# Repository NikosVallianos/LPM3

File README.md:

# LPM3 front-end #

The LPM3 is a device to measure light pollution on sea turtle nesting beaches. This repository focuses on the development of the front-end of the device, which can be used separately by any programmable device with an I²C and a SPI interface, such as an arduino, raspberry pi, or a suitable USB adapter.

The LPM3 front-end consists of a high sensitivity photometer and a regular sensitivity single-chip lux meter, an accelerometer, and a magnetometer all laid out on a single printed circuit board.

## Ultra-low dark current photodiode

The core of the LPM3 front-end is Hamamatsu's S1133, an ultra-low dark current visible light photodiode. A transimpedance amplifier with a 1GOhm feedback resistor gives a theoretical output of 1V per 0.164 lux. With a 12-bit ADC and a 2.5V reference, we can get a sensitivity of 0.0001 lux. The LPM3 is equipped with a 16-bit ADC, giving an absurd theoretical sensitivity of 0.00000625lux. Imperfections in the circuits and component manufacturing are expected to 

## Generic lux meter

The high sensitivity photodiode circuit is unable to measure any illuminance higher than 0.41lux. For this reason, and to serve as a crude source of self-calubration reference, the OPT3001 single-chip lux meter by Texas Instruments was incorporated in the LPM3 font-end. This lux meter is capable of measurements from 0.01 lux all the way up to daylight. This should cover all foreseeable light pollution conditions from pitch black all the way to in front of spotlights that are sometimes used to safeguard beach equipment.

## Accelerometer

All light pollution measurements should be taken at a horizontal plane, which is where hatchlings and sea turtles scan to perceive ambient light. An embedded accelerometer can either ensure this condition or be used to include device orientation in the dataset.

## Magnetometer

A magnetometer is the only way to know what direction a specific light pollution measurement was taken from.

## License
The LPM3 depository integrates hardware design, firmware source code, desktop software, and supporting documentation. These are licensed as follows:
- Hardware design files are licensed under the CERN Open Hardware License,
- Software source code files are licensed under the GNU GPL v3 license,
- Documentation files are licensed under the GNU Free Documentation License,
- Videos are licensed under Creative Commons Attribution-ShareAlike 4.0 International.

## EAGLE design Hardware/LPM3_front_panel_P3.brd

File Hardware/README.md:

This folder contains the hardware PCB design files, bill of materials, notes, data sheet links, and other details to help you manufacture a LPM3.
The hardware elements of the LPM3 project are licensed under the CERN Open Source Hardware license found here (link missing).

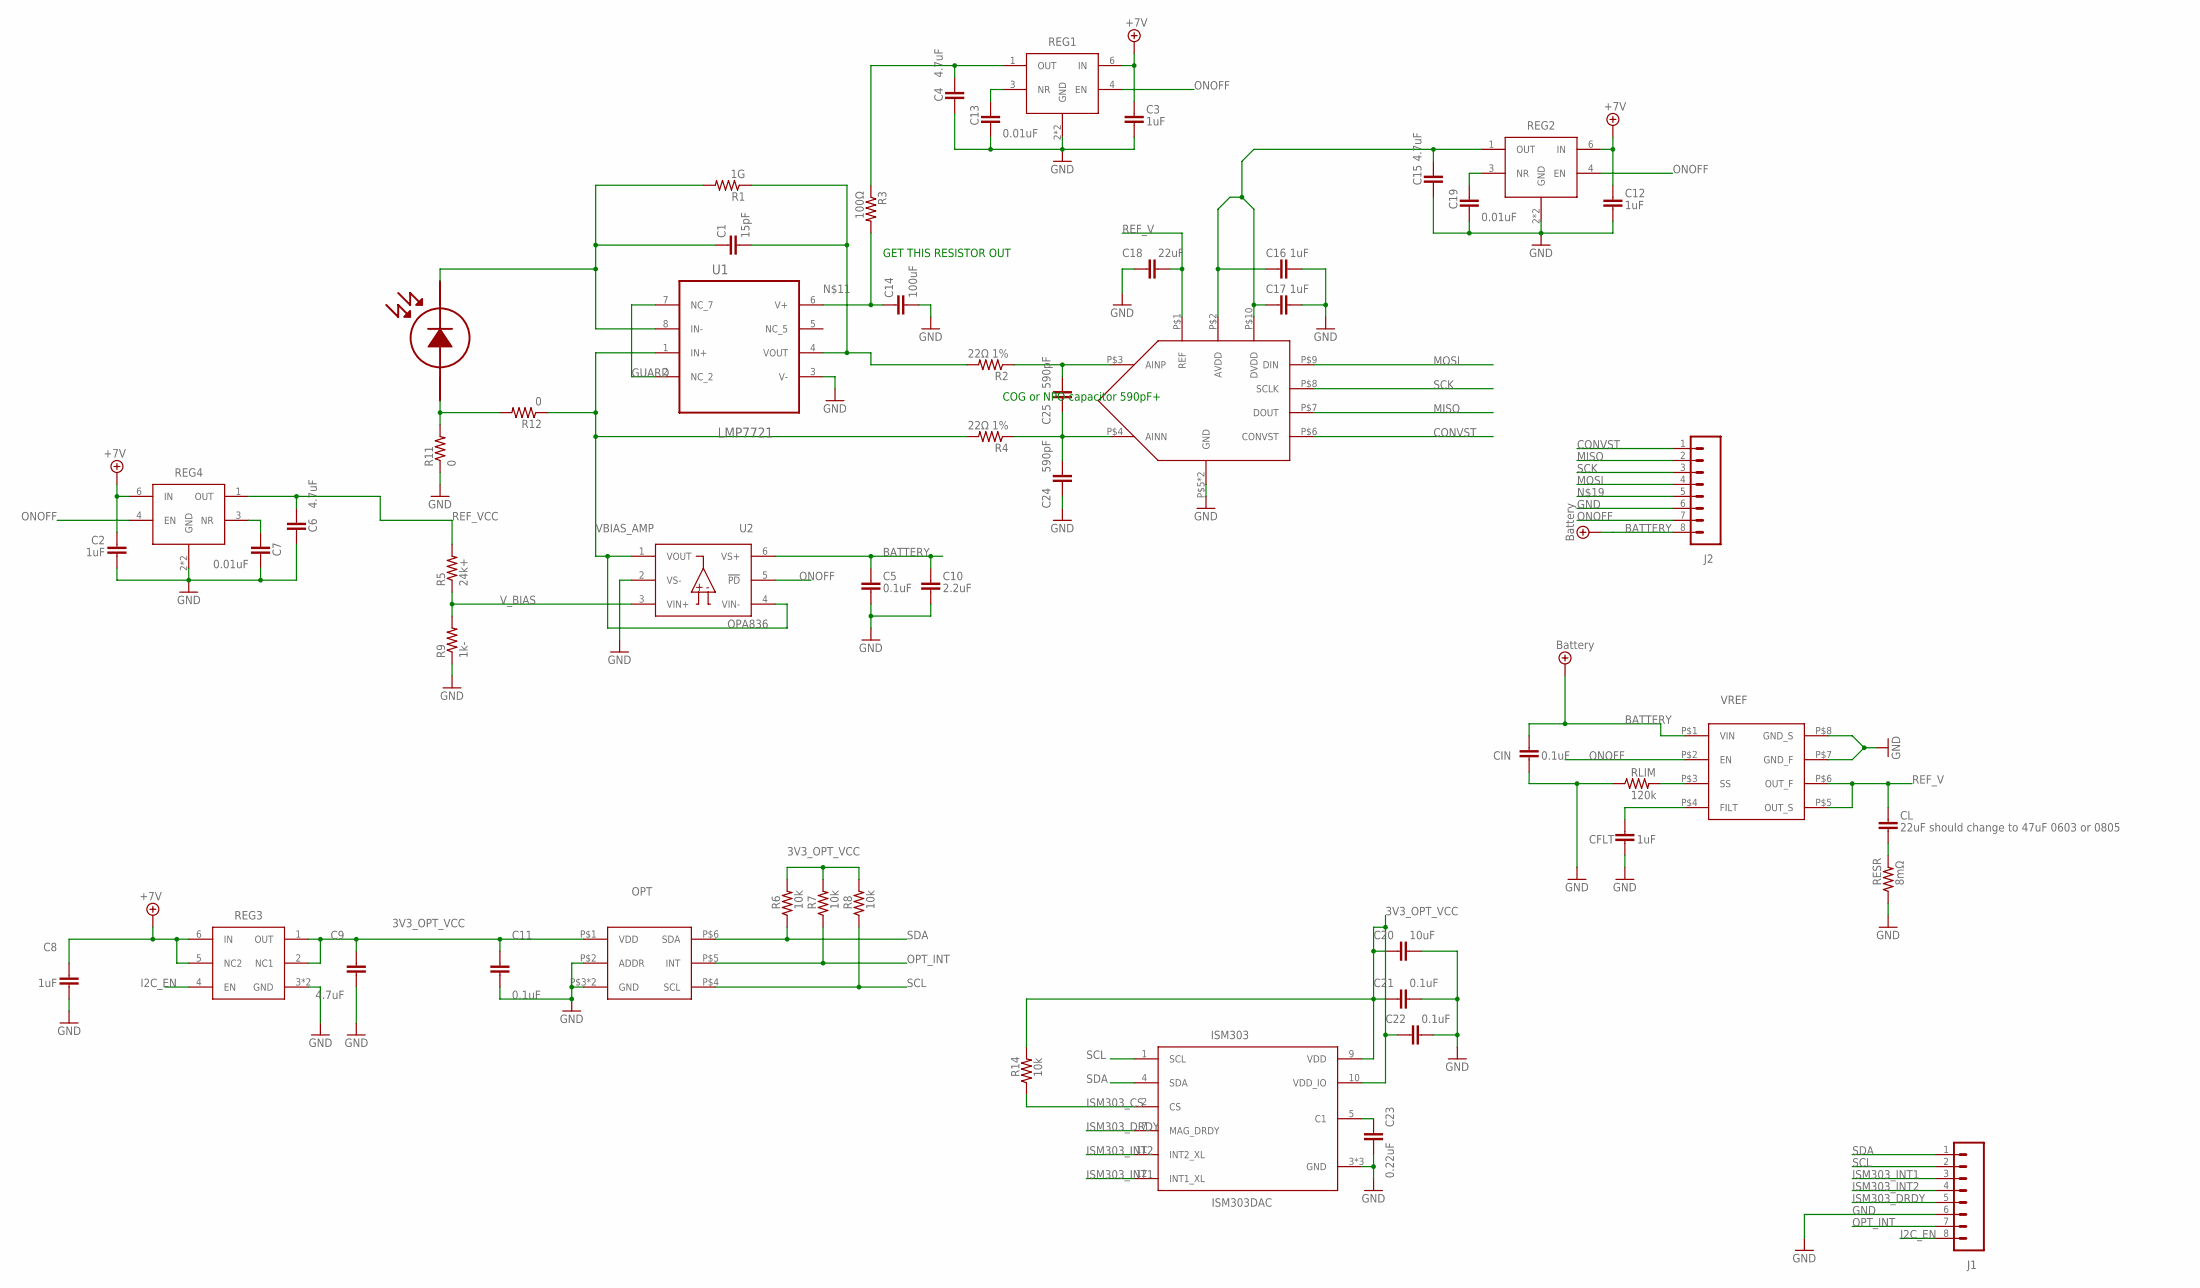
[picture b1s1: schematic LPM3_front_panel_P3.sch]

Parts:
ADC: ADS8866VSON10; VSON-10
C1: 15pF; 1206
C2, C3, C8, C12, C16, C17: 1uF; SMD_0402
C4, C6, C9, C15: 4.7uF; SMD_0402
C5, C11, C21, C22: 0.1uF; SMD_0402
C7, C13, C19: 0.01uF; SMD_0402
C10: 2.2uF; SMD_0402
C14: 100uF; 0805-CAP
C18: 22uF; SMD_0402
C20: 10uF; SMD_0402
C23: 0.22uF; SMD_0402
C24, C25: 590pF; SMD_0402
CFLT: 1uF; SMD_0402
CIN: 0.1uF; SMD_0402
CL: 22uF should change to 47uF 0603 or 0805; SMD_0402
D1: S1133_3; S1133_FLAT_SIDEWAYS
ISM303: ISM303DAC; LGA_12_ST
J1, J2: 8_PIN_0.05_INCH_SMD_FEMALE; 8_PIN_0.05"_SMD_ALTERN
OPT: OPT3001; USON-6-0.65-OPT3001
R1: 1G; 1206
R2, R4: 22Ω 1%; SMD_0402
R3: 100Ω; SMD_0402
R5: 24k+; SMD_0402
R6, R7, R8, R14: 10k; SMD_0402
R9: 1k-; SMD_0402
R11, R12: 0; SMD_0402
REG1, REG2, REG4: TPS717-Q1; WSON-6-1.5MM-NO-PAD
REG3: TPS706USON-6; USON-6-0.65
RESR: 8mΩ; SMD_0402
RLIM: 120k; SMD_0402
U1: LMP7721; SOIC127P600X175-8N
U2: OPA836; OPA836_SOT23
VREF: REF6225; VSSOP8

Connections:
3V3_OPT_VCC: C9.1, C11.1, C20.1, C21.1, C22.1, ISM303.9 (VDD), ISM303.10 (VDD_IO), OPT.P$1 (VDD), R6.1, R7.1, R8.1, R14.1, REG3.1 (OUT), REG3.2 (NC1)
BATTERY: C2.1, C3.1, C5.1, C8.1, C10.1, C12.1, CIN.1, J2.8, REG1.6 (IN), REG2.6 (IN), REG3.5 (NC2), REG3.6 (IN), REG4.6 (IN), U2.6 (VS+), VREF.P$1 (VIN)
CONVST: ADC.P$6 (CONVST), J2.1
FLT: CFLT.1, VREF.P$4 (FILT)
GND: ADC.P$5 (GND), ADC.P$PAD (GND), C2.2, C3.2, C4.2, C5.2, C6.2, C7.2, C8.2, C9.2, C10.2, C11.2, C12.2, C13.2, C14.2, C15.2, C16.2, C17.2, C18.1, C19.2, C20.2, C21.2, C22.2, C23.2, C24.1, CFLT.2, CIN.2, ISM303.3 (GND), ISM303.6 (GND), ISM303.8 (GND), J1.6, J2.6, OPT.P$2 (ADDR), OPT.P$3 (GND), OPT.PAD (GND), R9.2, R11.2, REG1.2 (GND), REG1.5 (GND), REG2.2 (GND), REG2.5 (GND), REG3.3 (GND), REG3.PAD (GND), REG4.2 (GND), REG4.5 (GND), RESR.2, RLIM.2, U1.3 (V-), U2.2 (VS-), VREF.P$7 (GND_F), VREF.P$8 (GND_S)
GUARD: U1.2 (NC_2), U1.7 (NC_7)
I2C_EN: J1.8, REG3.4 (EN)
ISM303_CS: ISM303.2 (CS), R14.2
ISM303_DRDY: ISM303.7 (MAG_DRDY), J1.5
ISM303_INT1: ISM303.12 (INT1_XL), J1.3
ISM303_INT2: ISM303.11 (INT2_XL), J1.4
MISO: ADC.P$7 (DOUT), J2.2
MOSI: ADC.P$9 (DIN), J2.4
unnamed: ADC.P$3 (AINP), C25.2, R2.2
unnamed: CL.2, RESR.1
unnamed: C1.P$1 (1), D1.CATHODE, R1.P$1 (1), U1.8 (IN-)
unnamed: C19.1, REG2.3 (NR)
unnamed: D1.ANODE, R11.1, R12.1
unnamed: C14.1, R3.1, U1.6 (V+)
unnamed: ADC.P$4 (AINN), C24.2, C25.1, R4.2
unnamed: C23.1, ISM303.5 (C1)
unnamed: C7.1, REG4.3 (NR)
unnamed: C13.1, REG1.3 (NR)
ONOFF: J2.7, REG1.4 (EN), REG2.4 (EN), REG4.4 (EN), U2.5 (!PD!), VREF.P$2 (EN)
OPAMP_VCC: C4.1, R3.2, REG1.1 (OUT)
OPT_INT: J1.7, OPT.P$5 (INT), R7.2
REF_V: ADC.P$1 (REF), C18.2, CL.1, VREF.P$5 (OUT_S), VREF.P$6 (OUT_F)
REF_VCC: C6.1, R5.1, REG4.1 (OUT)
SCK: ADC.P$8 (SCLK), J2.3
SCL: ISM303.1 (SCL), J1.2, OPT.P$4 (SCL), R8.2
SDA: ISM303.4 (SDA), J1.1, OPT.P$6 (SDA), R6.2
SS: RLIM.1, VREF.P$3 (SS)
TIA_OUT: C1.P$2 (2), R1.P$2 (2), R2.1, U1.4 (VOUT)
VBIAS_AMP: R4.1, R12.2, U1.1 (IN+), U2.1 (VOUT), U2.4 (VIN-)
VCC_ADC: ADC.P$2 (AVDD), ADC.P$10 (DVDD), C15.1, C16.1, C17.1, REG2.1 (OUT)
V_BIAS: R5.2, R9.1, U2.3 (VIN+)

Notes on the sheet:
GET THIS RESISTOR OUT
COG or NPO capacitor 590pF+

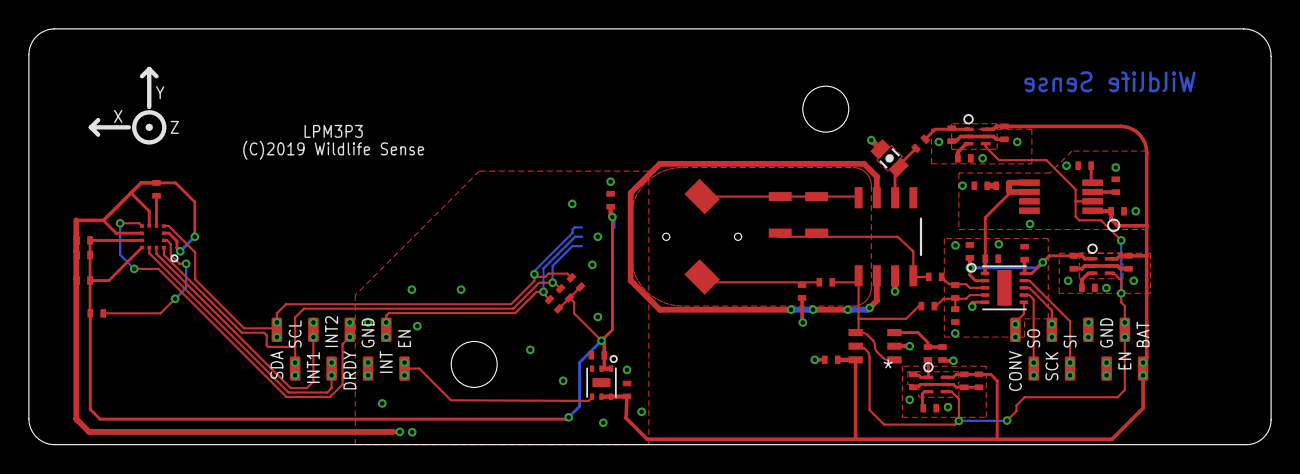
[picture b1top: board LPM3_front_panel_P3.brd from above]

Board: 2 copper layers, 86.5 x 29.0 mm, 55 parts (1 on the bottom side), 36 nets.

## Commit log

2019-09-21 Eagle pcb design files for the front panel
2019-09-21 Rename LPS3P3.brd to LPM3_front_panel_P3.brd
2019-09-21 Rename LPS3P3.sch to LPM3_front_panel_P3.sch
2019-09-21 Added initial licensing information on README.md
2020-04-04 Incremental edits

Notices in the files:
Hardware/LPM3_front_panel_P3.brd:
(C)2019 Wildlife Sense
parts and their libraries:
SparkFun-Capacitors: Licensing: Creative Commons ShareAlike 4.0 International - https://creativecommons.org/licenses/by-sa/4.0
